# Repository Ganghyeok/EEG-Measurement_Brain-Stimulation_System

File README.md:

# EEG-Measurement_Brain-Stimulation_System

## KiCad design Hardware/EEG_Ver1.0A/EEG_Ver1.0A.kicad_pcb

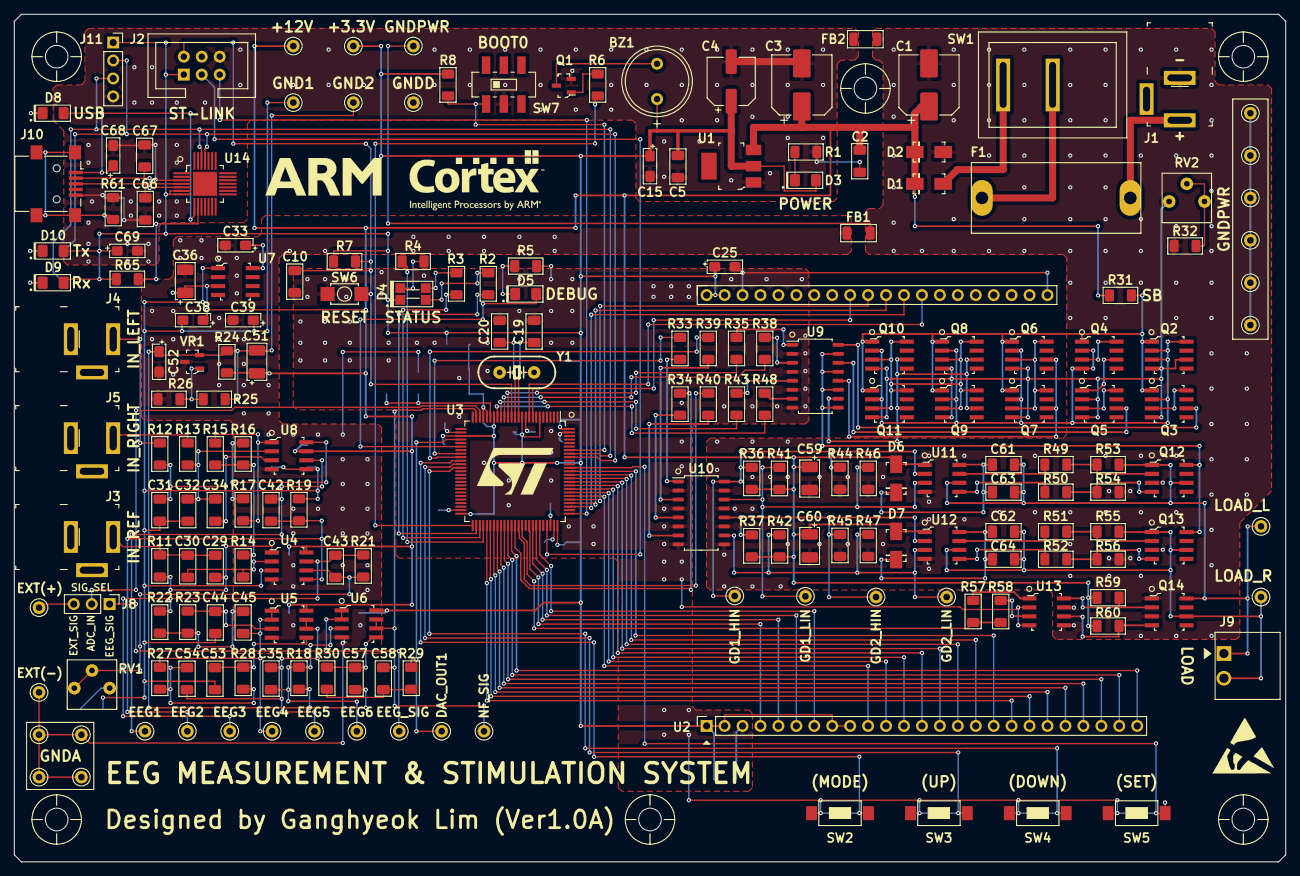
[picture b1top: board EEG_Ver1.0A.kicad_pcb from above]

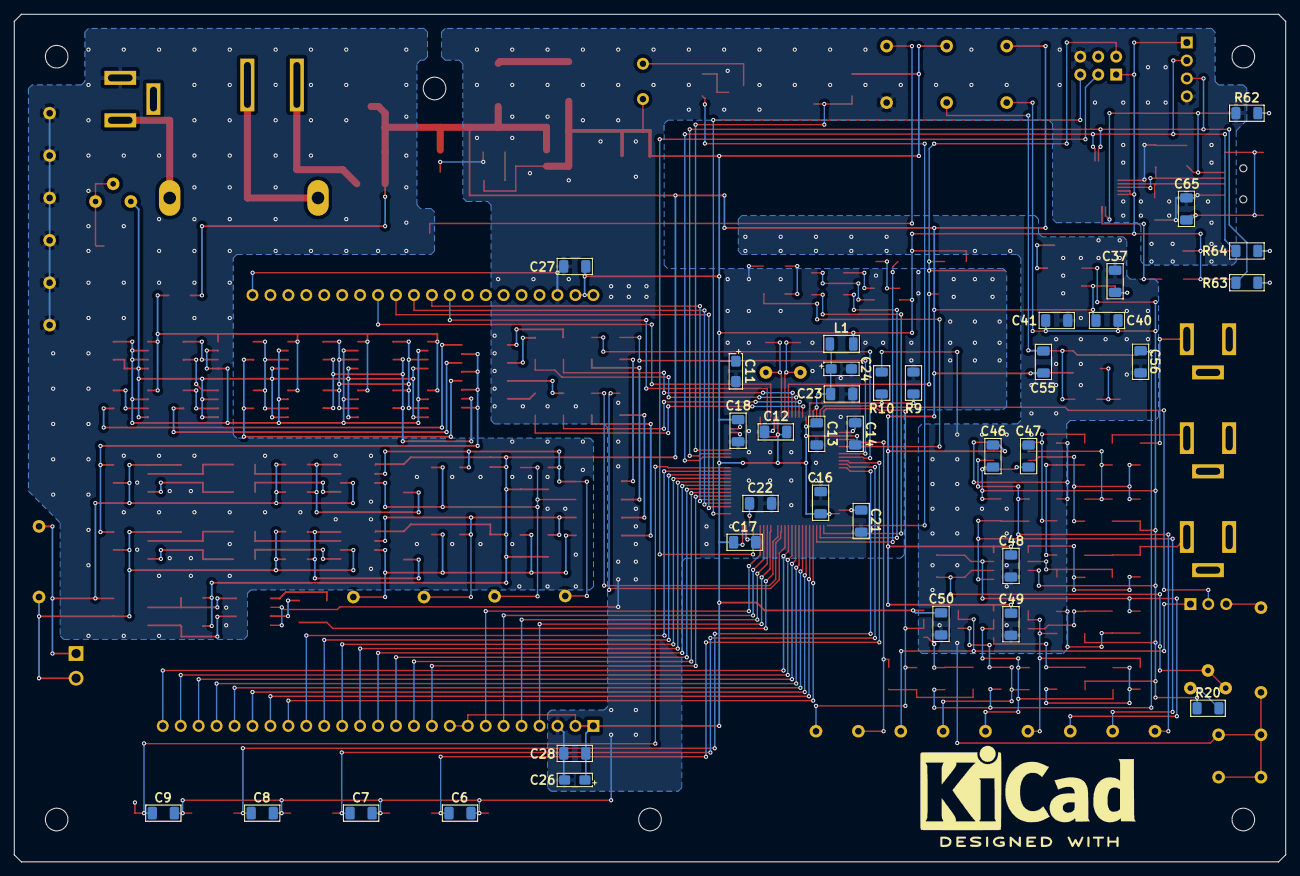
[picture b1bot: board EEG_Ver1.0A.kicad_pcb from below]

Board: 2 copper layers, 180.0 x 120.0 mm, 230 parts (36 on the bottom side), 154 nets.

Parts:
BZ1: Buzzer; FQ-013
C1, C3: 100uF/25V; CP_Elec_8x6.2
C2, C5, C10, C12, C13, C14, C16, C17, C18, C23, C27, C28, C34, C37, C40, C41, C46, C47, C48, C49, C50, C55, C56, C63, C64, C65: 100nF; C3216_Metric
C4: 100uF/16V; CP_Elec_6.3x5.3
C6, C7, C8, C9: 220nF; C3216_Metric
C11, C15, C25, C26, C38, C39, C52: 10uF/16V; C3216_Tantal_Metric
C19, C20: 20pF; C3216_Metric
C21, C22, C61, C62: 2.2uF; C3216_Metric
C24, C33, C68, C69: 1uF/16V; C3216_Tantal_Metric
C29, C30, C31, C32, C43: 1nF; C3216_Metric
C35, C42: 0.47uF; C3216_Metric
C36, C51, C59, C60: 10uF/25V; C3528_Tantal_Metric
C44, C45, C53, C54, C57, C58: 1uF; C3216_Metric
C66, C67: 15pF; C3216_Metric
D1: SS13; DO-214AC
D2: SMAJ12A; DO-214AC
D3: LED(GREEN); LED_3216_Metric
D4: EASR3212RGBA0
D5, D9, D10: LED(BLUE); LED_3216_Metric
D6, D7: SS14; DO-214AC
D8: LED(RED); LED_3216_Metric
F1: 250V/500mA; GF-205B(20mm)
FB1, FB2: BLM31PG391SH1L; L3216_Metric
J1: Power Connector; Barrel_Jack_5.5mmODx2.1mmID_PJ-202A
J2: ST-Link Connector; BHS-01-6P
J3: IN_REF_Connector; Barrel_Jack_5.5mmODx2.1mmID_PJ-202A
J4: IN_LEFT_Connector; Barrel_Jack_5.5mmODx2.1mmID_PJ-202A
J5: IN_RIGHT_Connector; Barrel_Jack_5.5mmODx2.1mmID_PJ-202A
J6: EXT_Connector(+); Test_Point(Loop)
J7: EXT_Connector(-); Test_Point(Loop)
J8: Sig_Selector; PinHeader_1x03_P2.54mm_Vertical
J9: Load_Connector; MOLEX_0395021002
J10: USB_B_Mini; USB_Mini-B_Lumberg_2486_01_Horizontal
J11: UART_Connector; PinSocket_1x04_P2.54mm_Vertical
L1: 10uH; L3216_Metric
Q1: 2SC1815; SOT-23-3
Q2, Q3, Q4, Q5, Q6, Q7, Q8, Q9, Q10, Q11: IRF7316; SOIC-8_W3.9mm
Q12, Q13, Q14: IRF7351; SOIC-8_W3.9mm
R1: 150; R3216_Metric
R2, R33, R34, R35, R38, R39, R40, R43, R48: 180; R3216_Metric
R3: 360; R3216_Metric
R4: 120; R3216_Metric
R5, R62, R63, R64: 330; R3216_Metric
R6: 2.7k; R3216_Metric
R7: 100k; R3216_Metric
R8, R14, R26, R44, R45, R46, R47, R53, R54, R55, R56: 10k; R3216_Metric
R9, R10, R31: 0(SB); R3216_Metric
R11: 200k; R3216_Metric
R12, R13: 2.2k; R3216_Metric
R15, R16: 200; R3216_Metric
R17: 100; R3216_Metric
R18, R19: 2M; R3216_Metric
R20: 39k; R3216_Metric
R21: 3.9M; R3216_Metric
R22, R23, R27, R28, R29, R30: 3.9k; R3216_Metric
R24: 500; R3216_Metric
R25: 3k; R3216_Metric
R32, R36, R37, R41, R42: 5k; R3216_Metric
R49, R50, R51, R52: 22; R3216_Metric
R57, R58: 180(ED); R3216_Metric
R59, R60: 5k(ED); R3216_Metric
R61: 1M; R3216_Metric
R65: 4.7k; R3216_Metric
RV1, RV2: R_VAR; Tocos_GF063P
SW1: SW(POWER); KCD1-101A
SW2: SW(MODE); ITS-1107(SMD)
SW3: SW(UP); ITS-1107(SMD)
SW4: SW(DOWN); ITS-1107(SMD)
SW5: SW(SET); ITS-1107(SMD)
SW6: SW(RESET); SW_TACT_SMD_W3.9mm_L2.9mm_H2mm_GH
SW7: SW(BOOT0); SW_Slide_6P_SMD_GH
TP1: TP(+12V); Test_Point(Loop)
TP2: TP(+3.3V); Test_Point(Loop)
TP3, TP24, TP25, TP26, TP27, TP28, TP31: TP(GNDPWR); Test_Point(Loop)
TP4: TP(GNDD); Test_Point(Loop)
TP5: TP(EEG6); Test_Point(Loop)
TP6: TP(EEG1); Test_Point(Loop)
TP7: TP(EEG_SIG); Test_Point(Loop)
TP8: TP(EEG2); Test_Point(Loop)
TP9: TP(GND1); Test_Point(Loop)
TP10: TP(EEG3); Test_Point(Loop)
TP11: TP(EEG4); Test_Point(Loop)
TP12, TP13, TP15, TP17: TP(GNDA); Test_Point(Loop)
TP14: TP(GND2); Test_Point(Loop)
TP16: TP(EEG5); Test_Point(Loop)
TP18: TP(DAC_OUT1); Test_Point(Loop)
TP19: TP(NF_SIG); Test_Point(Loop)
TP20: TP(GD1_HIN); Test_Point(Loop)
TP21: TP(GD2_HIN); Test_Point(Loop)
TP22: TP(GD1_LIN); Test_Point(Loop)
TP23: TP(GD2_LIN); Test_Point(Loop)
TP29: TP(LOAD_L); Test_Point(Loop)
TP30: TP(LOAD_R); Test_Point(Loop)
U1: LD1117S33TR; SOT-223
U2: TFT-32A
U3: STM32F407VGT6; LQFP-100_14x14mm_P0.5mm
U4, U5, U6: TLV2171; SOIC-8_W3.9mm
U7: TLE2426; SOIC-8_W3.9mm
U8: INA126; SOIC-8_W3.9mm
U9, U10: TCMT4100; SOIC-16_4.55x10.3mm_P1.27mm
U11, U12: IR2101; SOIC-8_W3.9mm
U13: MOCD217M; SOIC-8_W3.9mm
U14: CP2102; VFQFN-28-1EP_5x5mm_HandSolder
VR1: AZ431L; SOT-23-3
Y1: 8MHz; CRYSTAL_HC49_PTH

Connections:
+3V3: BZ1.1, C4.1, C5.1, C11.1, C12.1, C13.1, C14.1, C15.1, C16.1, C17.1, C18.1, C25.1, C26.1, C27.1, C28.1, C50.1, C69.1, D3.2, D4.1, D9.2, D10.2, J2.1, J11.1, L1.2, R7.1, R8.1, R65.2, TP2.1, U1.2, U2.1, U2.2, U2.8, U2.9, U2.26, U2.27, U3.6, U3.11, U3.19, U3.28, U3.50, U3.75, U3.100, U6.8, U14.6, U14.7
+12V: C1.1, C2.1, C3.1, C36.1, C37.1, C38.1, C40.1, C46.1, C48.1, C49.1, C51.1, C55.1, C59.1, C60.1, D1.K, D2.K, D6.A, D7.A, R24.2, R31.1, R36.2, R37.2, R41.2, R42.2, R59.2, R60.2, TP1.1, U1.3, U4.8, U5.8, U7.3, U8.7, U11.1, U12.1
ADC_IN0: J8.2, U3.23
ADC_IN1: C58.1, TP19.1, U3.24, U6.6, U6.7
BOOT0: R8.2, SW7.1, U3.94
BUZZER: R6.2, U3.51
CURRENT_DAC: Q12.8, Q13.8, U9.9, U9.11, U9.13, U9.15
D+: C66.2, J10.3, U14.4
D-: C67.2, J10.2, U14.5
DAC_OUT1: R29.2, TP18.1, U3.29
DEBUG1: D5.2, U3.31
EEG_SIG: J8.1, TP7.1, U6.1, U6.2
EXT_SIG: J6.1, J8.3
GD1_HIN: R36.1, R44.1, TP20.1, U10.16, U11.2
GD1_LIN: R41.1, R46.1, TP22.1, U10.14, U11.3
GD2_HIN: R37.1, R45.1, TP21.1, U10.12, U12.2
GD2_LIN: R42.1, R47.1, TP23.1, U10.10, U12.3
GND1: C31.2, C32.1, C38.2, C39.1, C40.2, C41.1, C44.1, C46.2, C47.1, C53.1, R19.1, R20.2, TP9.1, U4.3, U7.1, U8.5
GND2: C51.2, C52.1, C55.2, C56.1, C57.1, R18.2, R24.1, R25.1, TP14.1, VR1.2
GNDA: C33.2, C36.2, C37.2, C39.2, C41.2, C47.2, C48.2, C49.2, C50.2, C52.2, C56.2, FB1.1, J7.1, R10.1, R26.2, TP12.1, TP13.1, TP15.1, TP17.1, U4.4, U5.4, U6.4, U7.2, U8.4, VR1.3
GNDD: C2.2, C3.2, C4.2, C5.2, C6.2, C7.2, C8.2, C9.2, C10.2, C11.2, C12.2, C13.2, C14.2, C15.2, C16.2, C17.2, C18.2, C19.2, C20.2, C21.2, C22.2, C23.2, C24.2, C25.2, C26.2, C27.2, C28.2, C65.1, C66.1, C67.1, C68.2, C69.2, FB2.2, J2.6, J10.5, J11.4, Q1.2, R1.2, R5.2, R9.1, R61.1, R62.2, SW2.1, SW3.1, SW4.1, SW5.1, SW6.2, SW7.2, TP4.1, U1.1, U2.3, U2.28, U2.45, U3.10, U3.27, U3.74, U3.99, U9.2, U9.4, U9.6, U9.8, U10.2, U10.4, U10.6, U10.8, U13.2, U13.4, U14.3
GNDPWR: C1.2, C59.2, C60.2, D2.A, FB1.2, FB2.1, J1.2, Q12.3, Q13.3, Q14.1, Q14.3, R32.1, R44.2, R45.2, R46.2, R47.2, R54.1, R56.1, TP3.1, TP24.1, TP25.1, TP26.1, TP27.1, TP28.1, TP31.1, U10.9, U10.11, U10.13, U10.15, U11.4, U12.4, U13.5, U13.7
H_MOS1: Q12.2, R49.1, R53.2
H_MOS2: Q13.2, R51.1, R55.2
KEY1: C6.1, SW2.2, U3.35
KEY2: C7.1, SW3.2, U3.36
KEY3: C8.1, SW4.2, U3.37
KEY4: C9.1, SW5.2, U3.89
LOAD_L: C61.2, C63.2, J9.1, Q12.1, Q12.6, Q14.8, R53.1, TP29.1, U11.6
LOAD_R: C62.2, C64.2, J9.2, Q13.1, Q13.6, Q14.6, R55.1, TP30.1, U12.6
L_MOS1: Q12.4, R50.1, R54.2
L_MOS2: Q13.4, R52.1, R56.2
NRST: C10.1, J2.2, R7.2, SW6.1, U3.14
unnamed: BZ1.2, Q1.3
unnamed: C19.1, U3.12, Y1.1
unnamed: C20.1, U3.13, Y1.2
unnamed: C21.1, U3.49
unnamed: C22.1, U3.73
unnamed: C29.1, R11.2, U4.1
unnamed: C29.2, C30.2, J3.1, R11.1
unnamed: C30.1, R14.2, U4.2
unnamed: C31.1, C34.1, R12.2, U8.3
unnamed: C32.2, C34.2, R13.2, U8.2
unnamed: C33.1, U7.8
unnamed: C35.1, R18.1, TP5.1, U6.3
unnamed: C35.2, C54.2, TP16.1, U5.6, U5.7
unnamed: C42.1, R19.2, TP8.1, U4.5
unnamed: C42.2, TP6.1, U8.6
unnamed: C43.1, R21.1, R22.2, TP10.1, U4.7
unnamed: C43.2, R21.2, RV1.1, RV1.2, U4.6
unnamed: C44.2, R23.1, U5.3
unnamed: C45.1, R22.1, R23.2
unnamed: C45.2, R27.2, TP11.1, U5.1, U5.2
unnamed: C53.2, R28.1, U5.5
unnamed: C54.1, R27.1, R28.2
unnamed: C57.2, R30.1, U6.5
unnamed: C58.2, R29.1, R30.2
unnamed: C61.1, C63.1, D6.K, U11.8
unnamed: C62.1, C64.1, D7.K, U12.8
unnamed: C65.2, J10.6, R61.2
unnamed: D1.A, SW1.2
unnamed: D3.1, R1.1
unnamed: D4.2, R2.2
unnamed: D4.3, R3.2
unnamed: D4.4, R4.2
unnamed: D5.1, R5.1
unnamed: D8.1, R62.1
unnamed: D9.1, R63.2
unnamed: D10.1, R64.2
unnamed: F1.1, SW1.1
unnamed: F1.2, J1.1
unnamed: J4.1, R12.1
unnamed: J5.1, R13.1
unnamed: Q1.1, R6.1
unnamed: Q3.3, Q3.8
unnamed: Q3.6, U9.16
unnamed: Q4.3, Q4.8
unnamed: Q4.6, Q5.1
unnamed: Q5.3, Q5.8
unnamed: Q5.6, U9.14
unnamed: Q6.3, Q6.8, Q7.3, Q7.8
unnamed: Q6.6, Q7.6, U9.12
unnamed: Q2.1, Q3.1, Q4.1, Q6.1, Q7.1, Q8.1, Q9.1, Q10.1, Q11.1, R31.2
unnamed: Q2.2, Q2.3, Q2.8, Q3.2, Q4.2, Q4.4, Q6.2, Q7.2, Q8.2, Q9.2, Q10.2, Q11.2
unnamed: Q8.3, Q8.8, Q9.3, Q9.8, Q10.3, Q10.8, Q11.3, Q11.8
unnamed: Q2.4, Q2.6, Q3.4, Q5.2, Q5.4, Q6.4, Q7.4, Q8.4, Q9.4, Q10.4, Q11.4, RV2.1
unnamed: Q8.6, Q9.6, Q10.6, Q11.6, U9.10
unnamed: Q14.2, R59.1, U13.8
unnamed: Q14.4, R60.1, U13.6
unnamed: R9.2, R10.2, U3.20
unnamed: R14.1, R15.1, R16.1
unnamed: R15.2, R17.1, U8.1
unnamed: R16.2, R17.2, U8.8
unnamed: R20.1, RV1.3
unnamed: R25.2, R26.1, VR1.1
unnamed: R32.2, RV2.2, RV2.3
unnamed: R33.1, U10.1
unnamed: R34.1, U10.5
unnamed: R35.1, U9.1
unnamed: R38.1, U9.3
unnamed: R39.1, U10.3
unnamed: R40.1, U10.7
unnamed: R43.1, U9.5
unnamed: R48.1, U9.7
unnamed: R49.2, U11.7
unnamed: R50.2, U11.5
unnamed: R51.2, U12.7
unnamed: R52.2, U12.5
unnamed: R57.1, U13.1
unnamed: R58.1, U13.3
unnamed: R65.1, U14.9
OPTO1: R35.2, U3.15
OPTO2: R38.2, U3.16
OPTO3: R43.2, U3.17
OPTO4: R48.2, U3.18
SPI3_MISO: U2.36, U3.79
SPI3_MOSI: U2.35, U3.80
SPI3_SCK: U2.37, U3.78
SWCLK: J2.5, U3.76
SWDIO: J2.3, U3.72
TFT_D0: U2.10, U3.81
TFT_D1: U2.11, U3.82
TFT_D2: U2.12, U3.83
TFT_D3: U2.13, U3.84
TFT_D4: U2.14, U3.85
TFT_D5: U2.15, U3.86
TFT_D6: U2.16, U3.87
TFT_D7: U2.17, U3.88
TFT_D8: U2.18, U3.55
TFT_D9: U2.19, U3.56
TFT_D10: U2.20, U3.57
TFT_D11: U2.21, U3.58
TFT_D12: U2.22, U3.59
TFT_D13: U2.23, U3.60
TFT_D14: U2.24, U3.61
TFT_D15: U2.25, U3.62
TFT_RS: U2.6, U3.69
UART1_RX: J11.3, R63.1, U3.93, U14.26
UART1_TX: J11.2, R64.1, U3.92, U14.25
VBUS: C68.1, D8.2, J10.1, U14.8
VDDA: C23.1, C24.1, L1.1, U3.21, U3.22
~DISCHARGE: R57.2, R58.2, U3.65
~H_SIDE1: R33.2, U3.33
~H_SIDE2: R34.2, U3.63
~LED_BLUE: R4.1, U3.54
~LED_GREEN: R3.1, U3.53
~LED_RED: R2.1, U3.52
~L_SIDE1: R39.2, U3.34
~L_SIDE2: R40.2, U3.64
~TFT_CS: U2.5, U3.68
~TFT_RST: U2.4, U3.67
~TFT_WR: U2.7, U3.70
~TS_CS: U2.34, U3.8
~TS_INT: U2.38, U3.9

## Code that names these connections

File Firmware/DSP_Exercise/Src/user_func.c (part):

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
void BUZZER_Init(void)
{
	GPIO_InitTypeDef GPIO_BUZZER;

	memset(&GPIO_BUZZER, 0, sizeof(GPIO_BUZZER));

	GPIO_BUZZER.Mode = GPIO_MODE_OUTPUT_PP;
	GPIO_BUZZER.Speed = GPIO_SPEED_FREQ_VERY_HIGH;
	GPIO_BUZZER.Pin = GPIO_PIN_12;

	GPIO_Init(GPIOB, &GPIO_BUZZER);

	GPIO_WritePin(GPIOB, GPIO_PIN_12, GPIO_PIN_RESET);
}
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	GPIO_Init(GPIOC, &GPIO_GD);


	// 3. GPIO Init for Passive Discharge
	GPIO_InitTypeDef GPIO_PD;

	memset(&GPIO_PD, 0, sizeof(GPIO_PD));
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	while(1)
	{
		// 2. All OFF and Enable Passive Discharge
		GPIO_WritePin(GPIOC, GPIO_PIN_4, GPIO_PIN_SET);	// H_SIDE1 : LOW (-> H_MOS1 Turn OFF)
		GPIO_WritePin(GPIOC, GPIO_PIN_5, GPIO_PIN_SET);	// L_SIDE1 : LOW (-> L_MOS1 Turn OFF)
		GPIO_WritePin(GPIOC, GPIO_PIN_6, GPIO_PIN_SET);	// H_SIDE2 : LOW (-> H_MOS2 Turn OFF)
		GPIO_WritePin(GPIOC, GPIO_PIN_7, GPIO_PIN_SET);	// L_SIDE2 : LOW (-> L_MOS2 Turn OFF)
		Delay_us(10);
		GPIO_WritePin(GPIOC, GPIO_PIN_8, GPIO_PIN_RESET);	// Passive Discharge ON
		Delay_ms(4);
		GPIO_WritePin(GPIOC, GPIO_PIN_8, GPIO_PIN_SET);		// Passive Discharge OFF
		Delay_us(10);

		// 3. M1, M4 ON
		GPIO_WritePin(GPIOC, GPIO_PIN_4, GPIO_PIN_RESET);		// H_SIDE1 : HIGH (-> H_MOS1 Turn ON)
		GPIO_WritePin(GPIOC, GPIO_PIN_7, GPIO_PIN_RESET);		// L_SIDE2 : HIGH (-> L_MOS2 Turn ON)
		Delay_ms(1);

		// 4. All OFF for very short time
		GPIO_WritePin(GPIOC, GPIO_PIN_4, GPIO_PIN_SET);	// H_SIDE1 : LOW (-> H_MOS1 Turn OFF)
		GPIO_WritePin(GPIOC, GPIO_PIN_5, GPIO_PIN_SET);	// L_SIDE1 : LOW (-> L_MOS1 Turn OFF)
		GPIO_WritePin(GPIOC, GPIO_PIN_6, GPIO_PIN_SET);	// H_SIDE2 : LOW (-> H_MOS2 Turn OFF)
		GPIO_WritePin(GPIOC, GPIO_PIN_7, GPIO_PIN_SET);	// L_SIDE2 : LOW (-> L_MOS2 Turn OFF)
		Delay_us(100);

		// 5. M2, M3 ON
		GPIO_WritePin(GPIOC, GPIO_PIN_6, GPIO_PIN_RESET);		// H_SIDE2 : HIGH (-> H_MOS2 Turn On)
		GPIO_WritePin(GPIOC, GPIO_PIN_5, GPIO_PIN_RESET);		// L_SIDE1 : HIGH (-> L_MOS1 Turn On)
		Delay_ms(1);
	}
}
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	Delay_ms(1);

	// 3. M1, M4 ON
	GPIO_WritePin(GPIOC, GPIO_PIN_4, GPIO_PIN_RESET);		// H_SIDE1 : HIGH (-> H_MOS1 Turn ON)
	GPIO_WritePin(GPIOC, GPIO_PIN_7, GPIO_PIN_RESET);		// L_SIDE2 : HIGH (-> L_MOS2 Turn ON)
	Delay_ms(1);

	// 4. All OFF for very short time
	GPIO_WritePin(GPIOC, GPIO_PIN_4, GPIO_PIN_SET);	// H_SIDE1 : LOW (-> H_MOS1 Turn OFF)
	GPIO_WritePin(GPIOC, GPIO_PIN_5, GPIO_PIN_SET);	// L_SIDE1 : LOW (-> L_MOS1 Turn OFF)
	GPIO_WritePin(GPIOC, GPIO_PIN_6, GPIO_PIN_SET);	// H_SIDE2 : LOW (-> H_MOS2 Turn OFF)
	GPIO_WritePin(GPIOC, GPIO_PIN_7, GPIO_PIN_SET);	// L_SIDE2 : LOW (-> L_MOS2 Turn OFF)
	Delay_us(100);

	// 5. M2, M3 ON
	GPIO_WritePin(GPIOC, GPIO_PIN_6, GPIO_PIN_RESET);		// H_SIDE2 : HIGH (-> H_MOS2 Turn On)
	GPIO_WritePin(GPIOC, GPIO_PIN_5, GPIO_PIN_RESET);		// L_SIDE1 : HIGH (-> L_MOS1 Turn On)
	Delay_ms(1);

	// 6. All OFF and Enable Passive Discharge
	GPIO_WritePin(GPIOC, GPIO_PIN_4, GPIO_PIN_SET);	// H_SIDE1 : LOW (-> H_MOS1 Turn OFF)
	GPIO_WritePin(GPIOC, GPIO_PIN_5, GPIO_PIN_SET);	// L_SIDE1 : LOW (-> L_MOS1 Turn OFF)
	GPIO_WritePin(GPIOC, GPIO_PIN_6, GPIO_PIN_SET);	// H_SIDE2 : LOW (-> H_MOS2 Turn OFF)
	GPIO_WritePin(GPIOC, GPIO_PIN_7, GPIO_PIN_SET);	// L_SIDE2 : LOW (-> L_MOS2 Turn OFF)
	Delay_us(10);
	GPIO_WritePin(GPIOC, GPIO_PIN_8, GPIO_PIN_RESET);	// Passive Discharge ON
	Delay_ms(4);
	GPIO_WritePin(GPIOC, GPIO_PIN_8, GPIO_PIN_SET);		// Passive Discharge OFF
	Delay_us(10);
}

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	GPIO_WritePin(GPIOC, (GPIO_PIN_0 | GPIO_PIN_1 | GPIO_PIN_2 | GPIO_PIN_3), GPIO_PIN_RESET);

	// 2. Disable All MOSFETs of Bi-phasic Bipolar Current Driver
	GPIO_WritePin(GPIOC, GPIO_PIN_4, GPIO_PIN_SET);		// ~H_SIDE1 : HIGH (-> H_MOS1 Turn OFF)
	GPIO_WritePin(GPIOC, GPIO_PIN_5, GPIO_PIN_SET);		// ~L_SIDE1 : HIGH (-> L_MOS1 Turn OFF)
	GPIO_WritePin(GPIOC, GPIO_PIN_6, GPIO_PIN_SET);		// ~H_SIDE2 : HIGH (-> H_MOS2 Turn OFF)
	GPIO_WritePin(GPIOC, GPIO_PIN_7, GPIO_PIN_SET);		// ~L_SIDE2 : HIGH (-> L_MOS2 Turn OFF)

	// 3. Disable Passive Discharge
	GPIO_WritePin(GPIOC, GPIO_PIN_8, GPIO_PIN_SET);		// ~DISCHARGE : HIGH
}


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
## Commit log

2021-06-06 [End] Project End - perfect on Breadboard, but not perfect on PCB Version - LDL1117S33R needs heat plate. or add a linear regulator like 7805 Beacause of heat of LD1117S33R, 3.3V powerline is unstabl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
